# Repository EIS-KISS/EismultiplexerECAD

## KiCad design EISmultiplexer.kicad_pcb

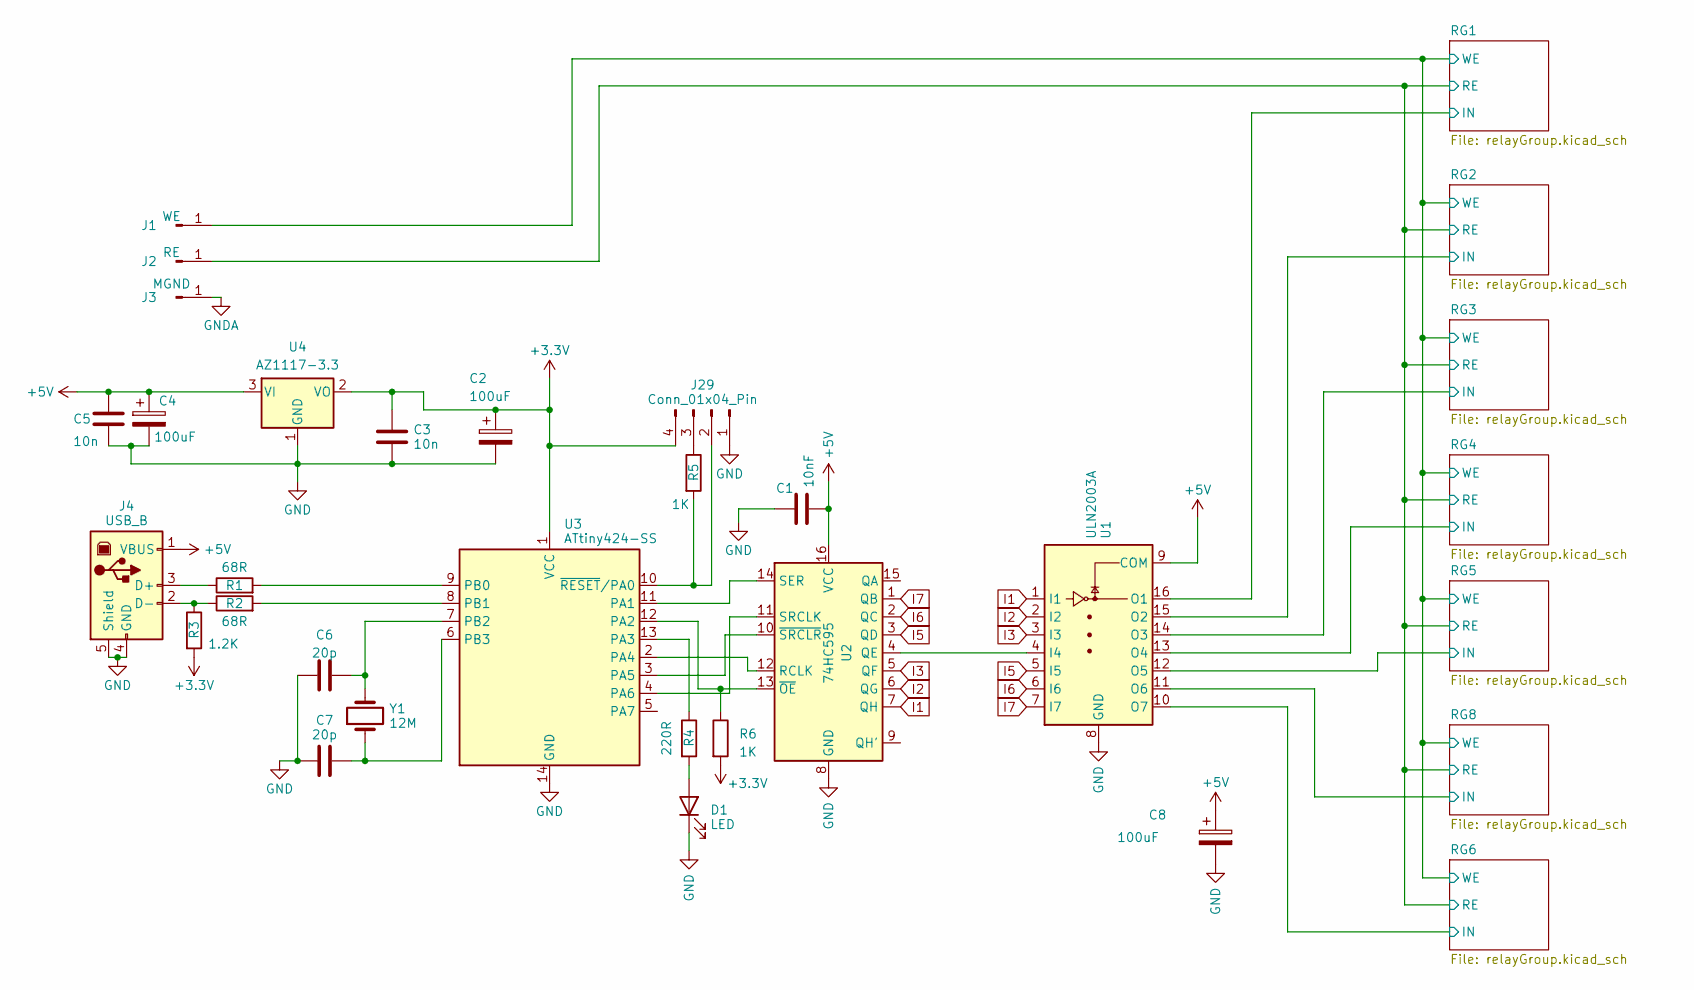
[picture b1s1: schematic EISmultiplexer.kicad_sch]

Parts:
C1: 10nF; C_Rect_L7.0mm_W6.0mm_P5.00mm
C2, C4, C8: 100uF; CP_Radial_D5.0mm_P2.00mm
C3, C5: 10n; C_Rect_L7.0mm_W6.0mm_P5.00mm
C6, C7: 20p; C_Disc_D3.8mm_W2.6mm_P2.50mm
D1: LED; LED_D3.0mm
J1: WE; BananaJack_HM_973582100
J2: RE; BananaJack_HM_973582100
J3: MGND; BananaJack_HM_973582100
J4: USB_B; USB_B_Wurth
J29: Conn_01x04_Pin; PinHeader_1x04_P2.54mm_Vertical
R1, R2: 68R; R_Axial_DIN0207_L6.3mm_D2.5mm_P10.16mm_Horizontal
R3: 1.2K; R_Axial_DIN0207_L6.3mm_D2.5mm_P10.16mm_Horizontal
R4: 220R; R_Axial_DIN0207_L6.3mm_D2.5mm_P10.16mm_Horizontal
R5, R6: 1K; R_Axial_DIN0207_L6.3mm_D2.5mm_P10.16mm_Horizontal
U1: ULN2003A; DIP-16_W7.62mm_LongPads
U2: 74HC595; DIP-16_W7.62mm_LongPads
U3: ATtiny424-SS; SOIC-14_3.9x8.7mm_P1.27mm
U4: AZ1117-3.3; SOT-223-3_TabPin2
Y1: 12M; Crystal_HC49-U_Vertical

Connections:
+3.3V: C2.1, C3.1, J29.4, R3.2, R6.2, U3.1 (VCC), U4.2 (VO)
+5V: C1.2, C4.1, C5.1, C8.1, J4.1 (VBUS), U1.9 (COM), U2.16 (VCC), U4.3 (VI); also elsewhere on the board
/RG1/IN: U1.16 (O1); also elsewhere on the board
/RG1/RE: J2.1; also elsewhere on the board
/RG1/WE: J1.1; also elsewhere on the board
/RG2/IN: U1.15 (O2); also elsewhere on the board
/RG3/IN: U1.14 (O3); also elsewhere on the board
/RG4/IN: U1.13 (O4); also elsewhere on the board
/RG5/IN: U1.12 (O5); also elsewhere on the board
/RG6/IN: U1.10 (O7); also elsewhere on the board
/RG8/IN: U1.11 (O6); also elsewhere on the board
GNDA: J3.1; also elsewhere on the board
I1: U1.1 (I1), U2.7 (QH)
I2: U1.2 (I2), U2.6 (QG)
I3: U1.3 (I3), U2.5 (QF)
I5: U1.5 (I5), U2.3 (QD)
I6: U1.6 (I6), U2.2 (QC)
I7: U1.7 (I7), U2.1 (QB)
unnamed: D1.2 (A), R4.2
unnamed: J4.3 (D+), R1.1
unnamed: J4.2 (D-), R2.1, R3.1
unnamed: J29.2, R5.2, U3.10 (~RESET/PA0)
unnamed: J29.3, R5.1
unnamed: U1.4 (I4), U2.4 (QE)
unnamed: U2.12 (RCLK), U3.2 (PA4)
unnamed: U2.14 (SER), U3.11 (PA1)
unnamed: U2.11 (SRCLK), U3.4 (PA6)
unnamed: R6.1, U2.13 (~OE), U3.12 (PA2)
unnamed: U2.10 (~SRCLR), U3.3 (PA5)
unnamed: R4.1, U3.13 (PA3)
unnamed: R1.2, U3.9 (PB0)
unnamed: R2.2, U3.8 (PB1)
unnamed: C6.1, U3.7 (PB2), Y1.2
unnamed: C7.1, U3.6 (PB3), Y1.1

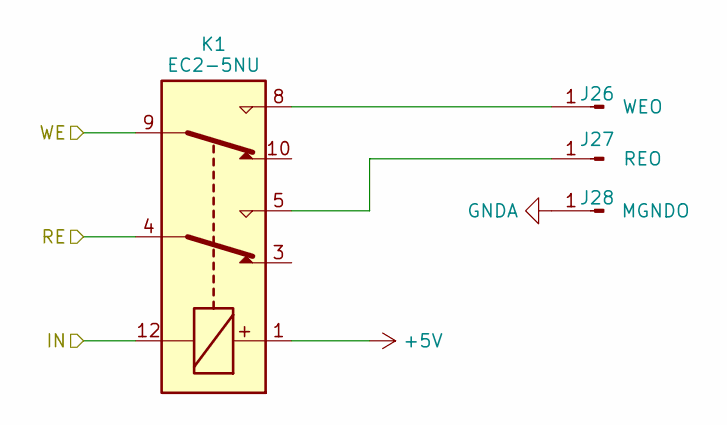
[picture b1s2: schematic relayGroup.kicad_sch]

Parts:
J26: WEO; BananaJack_HM_973582100
J27: REO; BananaJack_HM_973582100
J28: MGNDO; BananaJack_HM_973582100
K1: EC2-5NU; Relay_DPDT_Kemet_EC2

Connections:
+5V: J26.2, J28.2, K1.1; also elsewhere on the board
/RG1/IN: J26.9, J28.9, K1.12; also elsewhere on the board
/RG1/RE: K1.4; also elsewhere on the board
/RG1/WE: K1.9; also elsewhere on the board
/RG2/IN: J26.8, J28.8; also elsewhere on the board
/RG3/IN: J26.7, J28.7; also elsewhere on the board
/RG4/IN: J26.6, J28.6; also elsewhere on the board
/RG5/IN: J26.5, J28.5; also elsewhere on the board
/RG6/IN: J26.3, J28.3; also elsewhere on the board
/RG8/IN: J26.4, J28.4; also elsewhere on the board
unnamed 21: K1.5; also elsewhere on the board

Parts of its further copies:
J5, J8, J11, J14, J17, J20, J23: WEO; BananaJack_HM_973582100
J6, J9, J12, J15, J18, J21, J24: REO; BananaJack_HM_973582100
J7, J10, J13, J16, J19, J22, J25: MGNDO; BananaJack_HM_973582100
K2, K3, K4, K5, K6, K7: EC2-5NU; Relay_DPDT_Kemet_EC2

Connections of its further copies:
+5V: K2.1, K3.1, K4.1, K5.1, K6.1, K7.1; also elsewhere on the board
/RG1/RE: K2.4, K3.4, K4.4, K5.4, K6.4, K7.4; also elsewhere on the board
/RG1/WE: K2.9, K3.9, K4.9, K5.9, K6.9, K7.9; also elsewhere on the board
/RG2/IN: K2.12; also elsewhere on the board
/RG3/IN: K3.12; also elsewhere on the board
/RG4/IN: K4.12; also elsewhere on the board
/RG5/IN: K5.12; also elsewhere on the board
/RG6/IN: K7.12; also elsewhere on the board
/RG8/IN: K6.12; also elsewhere on the board
GNDA: J7.1, J10.1, J13.1, J16.1, J19.1, J22.1, J25.1; also elsewhere on the board
unnamed 21: J6.1; also elsewhere on the board
unnamed: J8.1, K2.8
unnamed: J9.1, K2.5
unnamed: J11.1, K3.8
unnamed: J12.1, K3.5
unnamed: J14.1, K4.8
unnamed: J15.1, K4.5
unnamed: J17.1, K5.8
unnamed: J18.1, K5.5
unnamed: J20.1, K6.8
unnamed: J21.1, K6.5
unnamed: J23.1, K7.8
unnamed: J24.1, K7.5

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
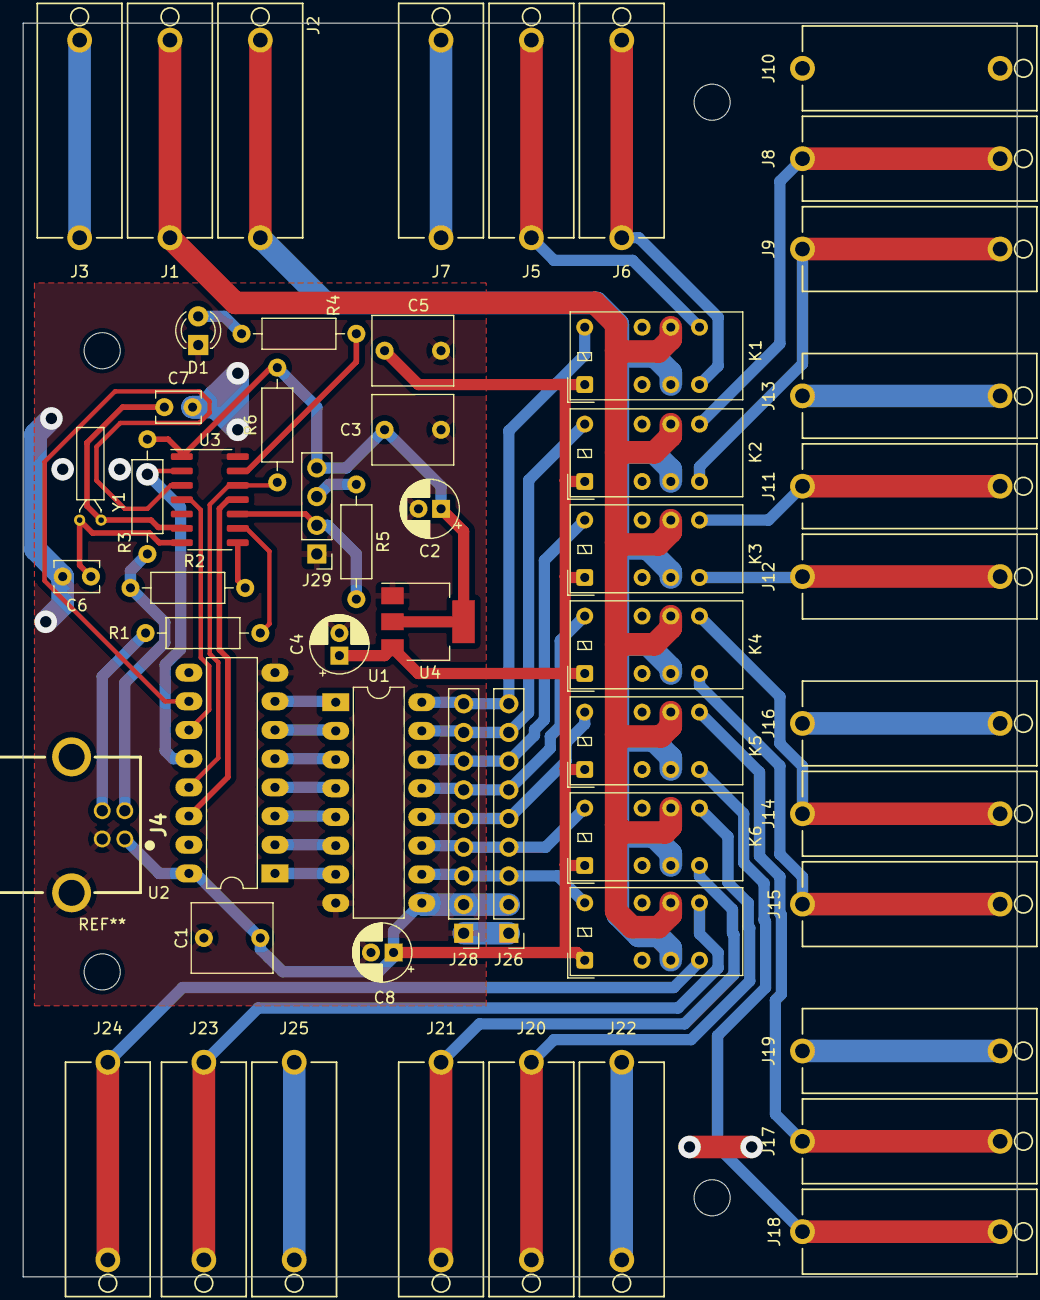
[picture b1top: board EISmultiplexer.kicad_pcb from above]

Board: 2 copper layers, 88.0 x 111.0 mm, 55 parts (0 on the bottom side), 49 nets.

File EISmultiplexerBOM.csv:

Item,Qty,Reference(s),Value,LibPart,Datasheet,Source
1,10,C1,10nF,Device:C,~,https://www.mouser.de/ProductDetail/Rubycon/25PX100MEFC5X11?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
2,20,"C2, C4, C8",100uF,Device:C_Polarized,~,https://www.mouser.de/ProductDetail/Rubycon/25PX100MEFC5X11?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
3,20,"C3, C5",10n,Device:C,~,https://www.mouser.de/ProductDetail/TDK/FG28C0G1H103JNT06?qs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
4,20,"C6, C7",20p,Device:C,~,https://www.mouser.de/ProductDetail/KEMET/C316C200KAG5TA?qs=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
5,10,D1,LED,Device:LED,~,STOCK
6,1,J4,USB_B,Connector:USB_B,~,STOCK
7,10,"J5, J8, J11, J14, J17, J20, J23",WEO,Connector:Conn_01x01_Pin,~,https://www.buerklin.com/en/p/hirschmann-test-measurement/la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
8,10,"J6, J9, J12, J15, J18, J21, J24",REO,Connector:Conn_01x01_Pin,~,https://www.buerklin.com/en/p/hirschmann-test-measurement/la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
9,10,"J7, J10, J13, J16, J19, J22, J25",MGNDO,Connector:Conn_01x01_Pin,~,https://www.buerklin.com/en/p/hirschmann-test-measurement/la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
10,10,J29,Conn_01x04_Pin,Connector:Conn_01x04_Pin,~,STOCK
11,20,"K1, K2, K3, K4, K5, K6, K7",EC2-5NU,Relay:EC2-5NU,https://content.kemet.com/datasheets/KEM_R7002_EC2_EE2.pdf,https://www.mouser.de/ProductDetail/KEMET/EC2-5NU?qs=iaWy59%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
12,20,"R1, R2",68R,Device:R,~,https://www.mouser.de/ProductDetail/YAGEO/MF0204FTE52-68R?qs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
13,20,R3,1.2K,Device:R,~,https://www.mouser.de/ProductDetail/YAGEO/MFR-25FTF52-1K2?qs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
14,20,R4,220R,Device:R,~,STOCK
15,20,R5,1K,Device:R,~,STOCK
16,10,U1,ULN2003A,Transistor_Array:ULN2003A,http://www.ti.com/lit/ds/symlink/uln2003a.pdf,https://www.mouser.de/ProductDetail/Texas-Instruments/ULN200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
17,10,U2,74HC595,74xx:74HC595,http://www.ti.com/lit/ds/symlink/sn74hc595.pdf,https://www.mouser.de/ProductDetail/Texas-Instruments/CD74HC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
18,5,U3,ATtiny424-SS,MCU_Microchip_ATtiny:ATtiny424-SS,https://ww1.microchip.com/downloads/en/DeviceDoc/ATtiny424-4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,https://www.mouser.de/ProductDetail/Microchip-Technology/ATT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
19,1,U4,AZ1117-3.3,Regulator_Linear:AZ1117-3.3,https://www.diodes.com/assets/Datasheets/AZ1117.pdf,STOCK
20,10,Y1,12M,Device:Crystal,~,https://www.mouser.de/ProductDetail/ECS/ECS-120-20-4X-EM?qs=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
21,10,,Vierkantmutter DIN562,,,https://online-schrauben.de/shop/Muttern/Vierkantmuttern/DIN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

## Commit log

2023-06-15 Inital commit
2023-06-16 add missing file
2023-06-16 Finalize Design
2023-06-16 Improve gnd net on pcb, reduce layer count to 2
2023-06-19 Move bannana jacks outward a bit
2023-06-20 Fix some minor DRC warnings
2023-08-28 Rev 1.0
2023-08-28 Replace crystal footprint, add stacking connector
